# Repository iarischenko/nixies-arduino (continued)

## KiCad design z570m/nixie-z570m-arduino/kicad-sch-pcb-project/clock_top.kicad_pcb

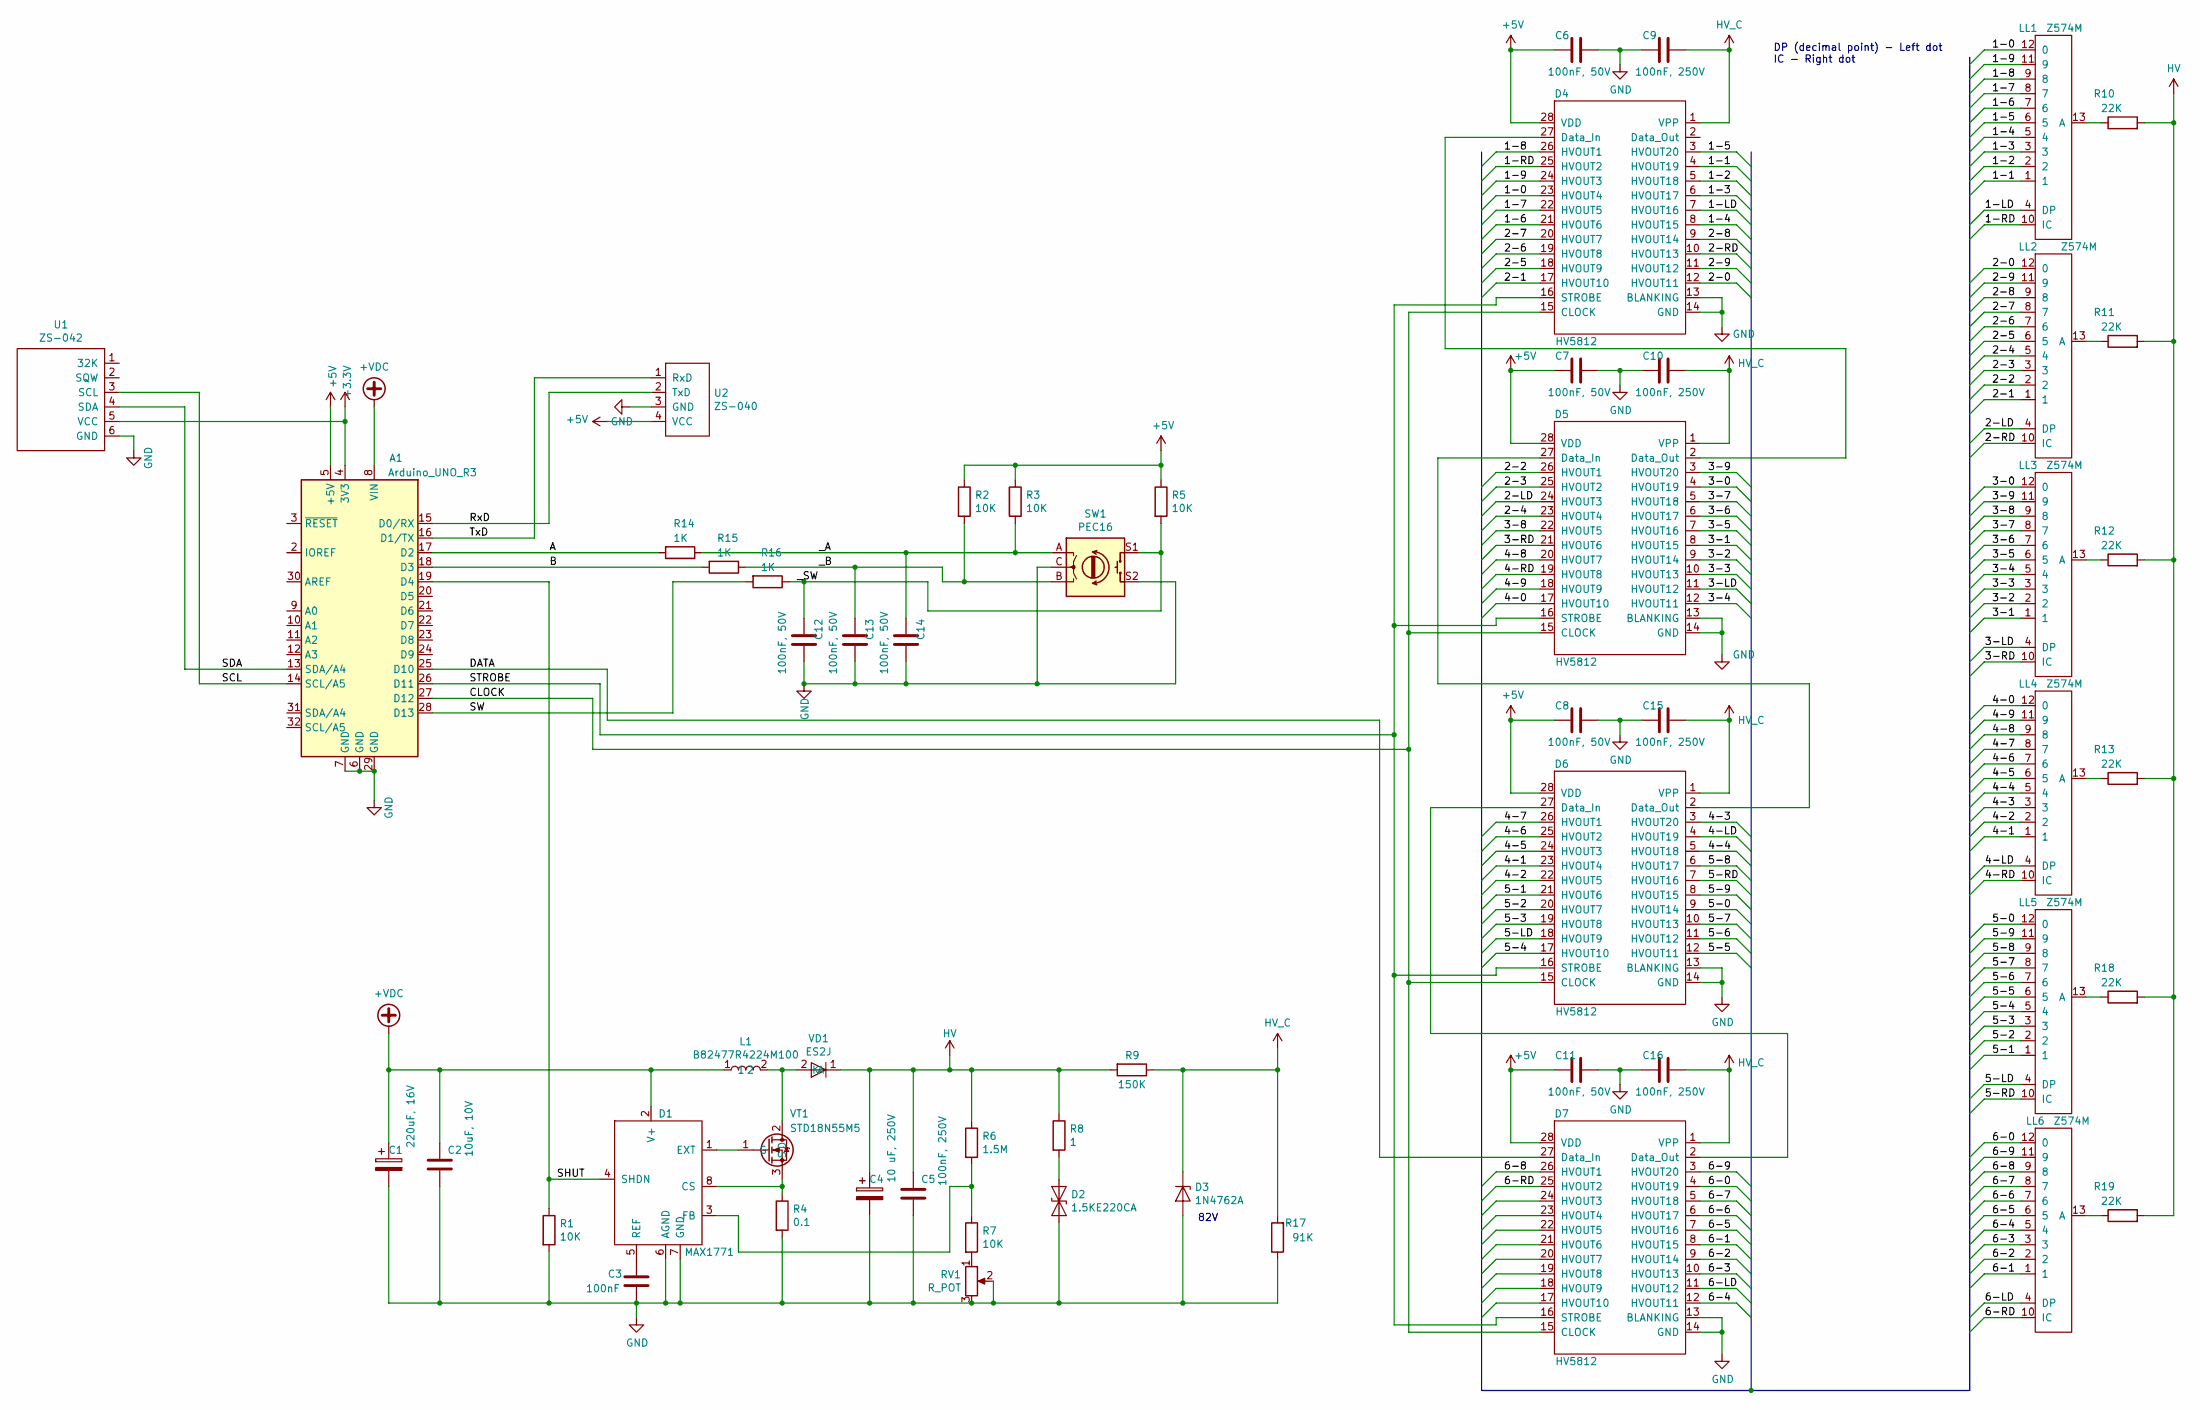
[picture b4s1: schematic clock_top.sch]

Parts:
A1: Arduino_UNO_R3
C1: 220uF, 16V; CP_Radial_D6.3mm_P2.50mm
C2: 10uF, 10V; C_1210_3225Metric_Pad1.42x2.65mm_HandSolder
C3: 100nF; C_0805_2012Metric_Pad1.15x1.40mm_HandSolder
C4: 10 uF, 250V; C_Axial_L22.0mm_D10.5mm_P27.50mm_Horizontal
C5, C9, C10, C15, C16: 100nF, 250V; C_1206_3216Metric_Pad1.42x1.75mm_HandSolder
C6, C7, C8, C11, C12, C13, C14: 100nF, 50V; C_0805_2012Metric_Pad1.15x1.40mm_HandSolder
D1: MAX1771; DIP-8_W7.62mm
D2: 1.5KE220CA; D_DO-201AE_P15.24mm_Horizontal
D3: 1N4762A; D_DO-41_SOD81_P10.16mm_Horizontal
D4, D5, D6, D7: HV5812; SOIC-28W_7.5x17.9mm_P1.27mm
L1: B82477R4224M100; L_12x12mm_H8mm
LL1, LL2, LL3, LL4, LL5, LL6: Z574M; Z570M
R1, R2, R3, R5, R7: 10K; R_0805_2012Metric_Pad1.15x1.40mm_HandSolder
R4: 0.1; R_2512_6332Metric_Pad1.52x3.35mm_HandSolder
R6: 1.5M; R_0805_2012Metric_Pad1.15x1.40mm_HandSolder
R8: 1; R_1206_3216Metric_Pad1.42x1.75mm_HandSolder
R9: 150K; R_0805_2012Metric_Pad1.15x1.40mm_HandSolder
R10, R11, R12, R13, R18, R19: 22K; R_0805_2012Metric_Pad1.15x1.40mm_HandSolder
R14, R15, R16: 1K; R_0805_2012Metric_Pad1.15x1.40mm_HandSolder
R17: 91K; R_0805_2012Metric_Pad1.15x1.40mm_HandSolder
RV1: R_POT; 3296W
SW1: PEC16; RotaryEncoder_Bouruns_PEC16
U1: ZS-042; zs-042
U2: ZS-040; zs-040
VD1: ES2J; D_SMB_Handsoldering
VT1: STD18N55M5; TO-252-2

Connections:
+3V3: A1.4 (3V3), U1.5 (VCC)
+5V: A1.5 (+5V), C6.2, C7.2, C8.2, C11.2, D4.28 (VDD), D5.28 (VDD), D6.28 (VDD), D7.28 (VDD), R2.1, R3.1, R5.1, U2.4 (VCC)
+VDC: A1.8 (VIN), C1.1, C2.1, D1.2 (V+), L1.1
/1-0: D4.23 (HVOUT4), LL1.12 (0)
/1-1: D4.4 (HVOUT19), LL1.1
/1-2: D4.5 (HVOUT18), LL1.2
/1-3: D4.6 (HVOUT17), LL1.3
/1-4: D4.8 (HVOUT15), LL1.5 (4)
/1-5: D4.3 (HVOUT20), LL1.6 (5)
/1-6: D4.21 (HVOUT6), LL1.7 (6)
/1-7: D4.22 (HVOUT5), LL1.8 (7)
/1-8: D4.26 (HVOUT1), LL1.9 (8)
/1-9: D4.24 (HVOUT3), LL1.11 (9)
/1-LD: D4.7 (HVOUT16), LL1.4 (DP)
/1-RD: D4.25 (HVOUT2), LL1.10 (IC)
/2-0: D4.12 (HVOUT11), LL2.12 (0)
/2-1: D4.17 (HVOUT10), LL2.1
/2-2: D5.26 (HVOUT1), LL2.2
/2-3: D5.25 (HVOUT2), LL2.3
/2-4: D5.23 (HVOUT4), LL2.5 (4)
/2-5: D4.18 (HVOUT9), LL2.6 (5)
/2-6: D4.19 (HVOUT8), LL2.7 (6)
/2-7: D4.20 (HVOUT7), LL2.8 (7)
/2-8: D4.9 (HVOUT14), LL2.9 (8)
/2-9: D4.11 (HVOUT12), LL2.11 (9)
/2-LD: D5.24 (HVOUT3), LL2.4 (DP)
/2-RD: D4.10 (HVOUT13), LL2.10 (IC)
/3-0: D5.4 (HVOUT19), LL3.12 (0)
/3-1: D5.8 (HVOUT15), LL3.1
/3-2: D5.9 (HVOUT14), LL3.2
/3-3: D5.10 (HVOUT13), LL3.3
/3-4: D5.12 (HVOUT11), LL3.5 (4)
/3-5: D5.7 (HVOUT16), LL3.6 (5)
/3-6: D5.6 (HVOUT17), LL3.7 (6)
/3-7: D5.5 (HVOUT18), LL3.8 (7)
/3-8: D5.22 (HVOUT5), LL3.9 (8)
/3-9: D5.3 (HVOUT20), LL3.11 (9)
/3-LD: D5.11 (HVOUT12), LL3.4 (DP)
/3-RD: D5.21 (HVOUT6), LL3.10 (IC)
/4-0: D5.17 (HVOUT10), LL4.12 (0)
/4-1: D6.23 (HVOUT4), LL4.1
/4-2: D6.22 (HVOUT5), LL4.2
/4-3: D6.3 (HVOUT20), LL4.3
/4-4: D6.5 (HVOUT18), LL4.5 (4)
/4-5: D6.24 (HVOUT3), LL4.6 (5)
/4-6: D6.25 (HVOUT2), LL4.7 (6)
/4-7: D6.26 (HVOUT1), LL4.8 (7)
/4-8: D5.20 (HVOUT7), LL4.9 (8)
/4-9: D5.18 (HVOUT9), LL4.11 (9)
/4-LD: D6.4 (HVOUT19), LL4.4 (DP)
/4-RD: D5.19 (HVOUT8), LL4.10 (IC)
/5-0: D6.9 (HVOUT14), LL5.12 (0)
/5-1: D6.21 (HVOUT6), LL5.1
/5-2: D6.20 (HVOUT7), LL5.2
/5-3: D6.19 (HVOUT8), LL5.3
/5-4: D6.17 (HVOUT10), LL5.5 (4)
/5-5: D6.12 (HVOUT11), LL5.6 (5)
/5-6: D6.11 (HVOUT12), LL5.7 (6)
/5-7: D6.10 (HVOUT13), LL5.8 (7)
/5-8: D6.6 (HVOUT17), LL5.9 (8)
/5-9: D6.8 (HVOUT15), LL5.11 (9)
/5-LD: D6.18 (HVOUT9), LL5.4 (DP)
/5-RD: D6.7 (HVOUT16), LL5.10 (IC)
/6-0: D7.4 (HVOUT19), LL6.12 (0)
/6-1: D7.8 (HVOUT15), LL6.1
/6-2: D7.9 (HVOUT14), LL6.2
/6-3: D7.10 (HVOUT13), LL6.3
/6-4: D7.12 (HVOUT11), LL6.5 (4)
/6-5: D7.7 (HVOUT16), LL6.6 (5)
/6-6: D7.6 (HVOUT17), LL6.7 (6)
/6-7: D7.5 (HVOUT18), LL6.8 (7)
/6-8: D7.26 (HVOUT1), LL6.9 (8)
/6-9: D7.3 (HVOUT20), LL6.11 (9)
/6-LD: D7.11 (HVOUT12), LL6.4 (DP)
/6-RD: D7.25 (HVOUT2), LL6.10 (IC)
/A: A1.17 (D2), R14.2
/B: A1.18 (D3), R15.2
/CLOCK: A1.27 (D12), D4.15 (CLOCK), D5.15 (CLOCK), D6.15 (CLOCK), D7.15 (CLOCK)
/DATA: A1.25 (D10), D7.27 (Data_In)
/RxD: A1.15 (D0/RX), U2.2 (TxD)
/SCL: A1.14 (SCL/A5), U1.3 (SCL)
/SDA: A1.13 (SDA/A4), U1.4 (SDA)
/SHUT: A1.19 (D4), D1.4 (SHDN), R1.1
/STROBE: A1.26 (D11), D4.16 (STROBE), D5.16 (STROBE), D6.16 (STROBE), D7.16 (STROBE)
/SW: A1.28 (D13), R16.2
/TxD: A1.16 (D1/TX), U2.1 (RxD)
/_A: C14.2, R3.2, R14.1, SW1.A
/_B: C13.2, R2.2, R15.1, SW1.B
/_SW: C12.2, R5.2, R16.1, SW1.S1
GND: A1.6 (GND), A1.7 (GND), A1.29 (GND), C1.2, C2.2, C3.2, C4.2, C5.2, C6.1, C7.1, C8.1, C9.2, C10.2, C11.1, C12.1, C13.1, C14.1, C15.2, C16.2, D1.6 (AGND), D1.7 (GND), D2.2 (A2), D3.2 (A), D4.13 (BLANKING), D4.14 (GND), D5.13 (BLANKING), D5.14 (GND), D6.13 (BLANKING), D6.14 (GND), D7.13 (BLANKING), D7.14 (GND), R1.2, R4.2, R17.1, RV1.2, RV1.3, SW1.C, SW1.S2, U1.6 (GND), U2.3 (GND)
HV: C4.1, C5.1, R6.1, R8.1, R9.2, R10.2, R11.2, R12.2, R13.2, R18.2, R19.2, VD1.1 (K)
HV_C: C9.1, C10.1, C15.1, C16.1, D3.1 (K), D4.1 (VPP), D5.1 (VPP), D6.1 (VPP), D7.1 (VPP), R9.1, R17.2
unnamed: C3.1, D1.5 (REF)
unnamed: D1.1 (EXT), VT1.1 (G)
unnamed: D1.3 (FB), R6.2, R7.1
unnamed: D1.8 (CS), R4.1, VT1.3 (S)
unnamed: D2.1 (A1), R8.2
unnamed: D4.27 (Data_In), D5.2 (Data_Out)
unnamed: D5.27 (Data_In), D6.2 (Data_Out)
unnamed: D6.27 (Data_In), D7.2 (Data_Out)
unnamed: L1.2, VD1.2 (A), VT1.2 (D)
unnamed: LL1.13 (A), R10.1
unnamed: LL2.13 (A), R11.1
unnamed: LL3.13 (A), R12.1
unnamed: LL4.13 (A), R13.1
unnamed: LL5.13 (A), R18.1
unnamed: LL6.13 (A), R19.1
unnamed: R7.2, RV1.1

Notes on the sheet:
DP (decimal point) - Left dot IC - Right dot
82V

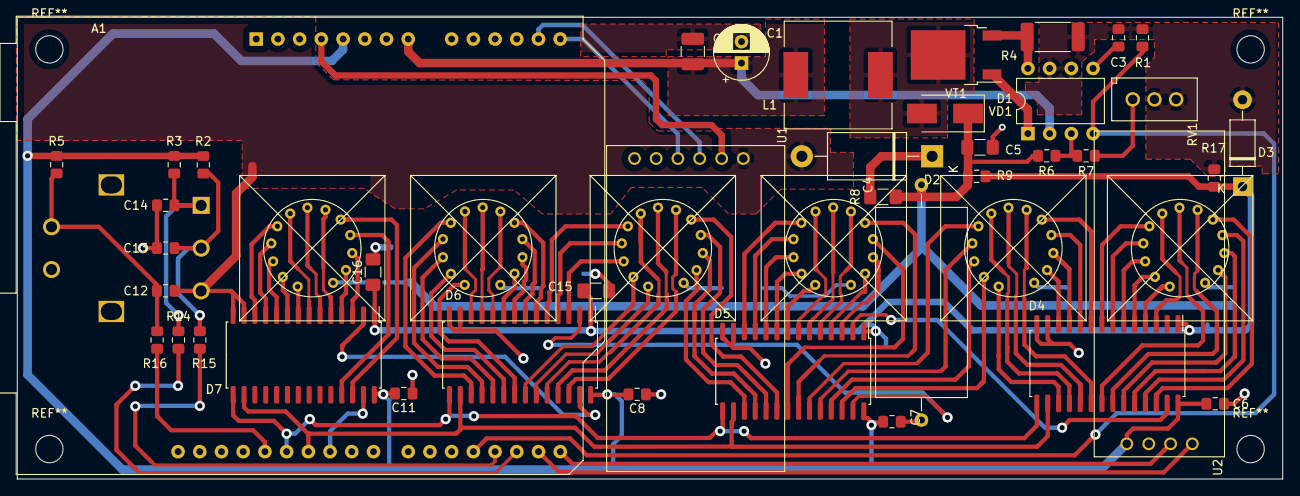
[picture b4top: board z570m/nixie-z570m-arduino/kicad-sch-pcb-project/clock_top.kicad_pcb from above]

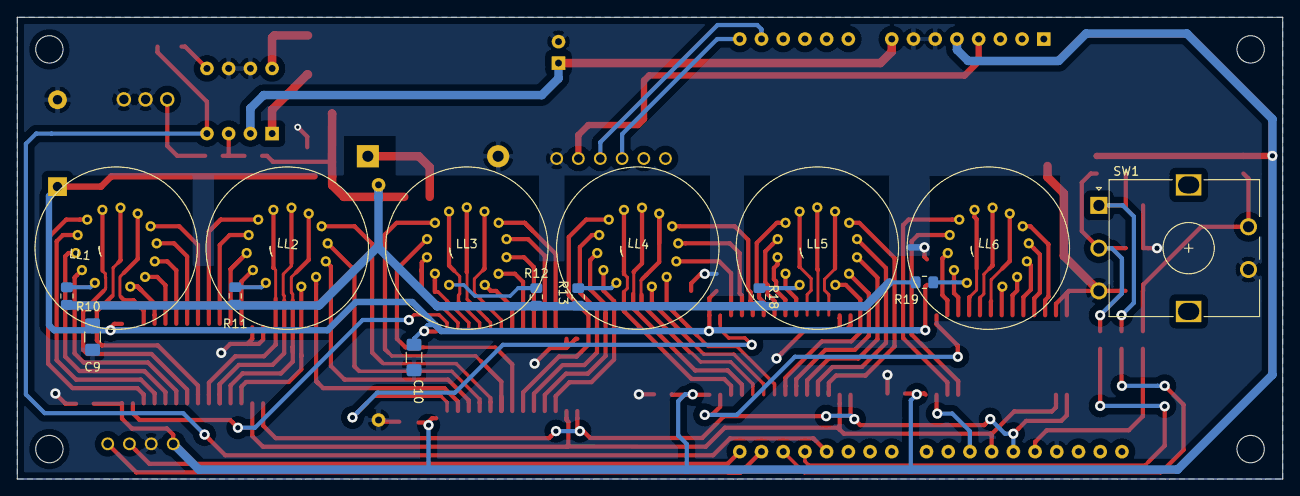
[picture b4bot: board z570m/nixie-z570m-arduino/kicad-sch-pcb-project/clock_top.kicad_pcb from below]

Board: 2 copper layers, 148.0 x 54.0 mm, 56 parts (15 on the bottom side), 108 nets.

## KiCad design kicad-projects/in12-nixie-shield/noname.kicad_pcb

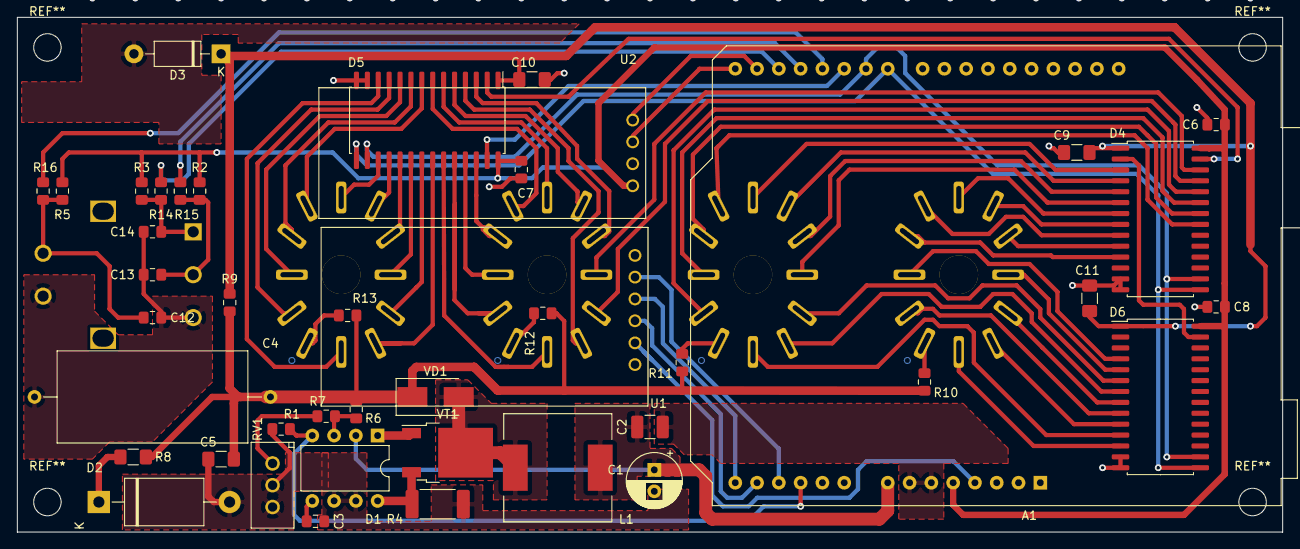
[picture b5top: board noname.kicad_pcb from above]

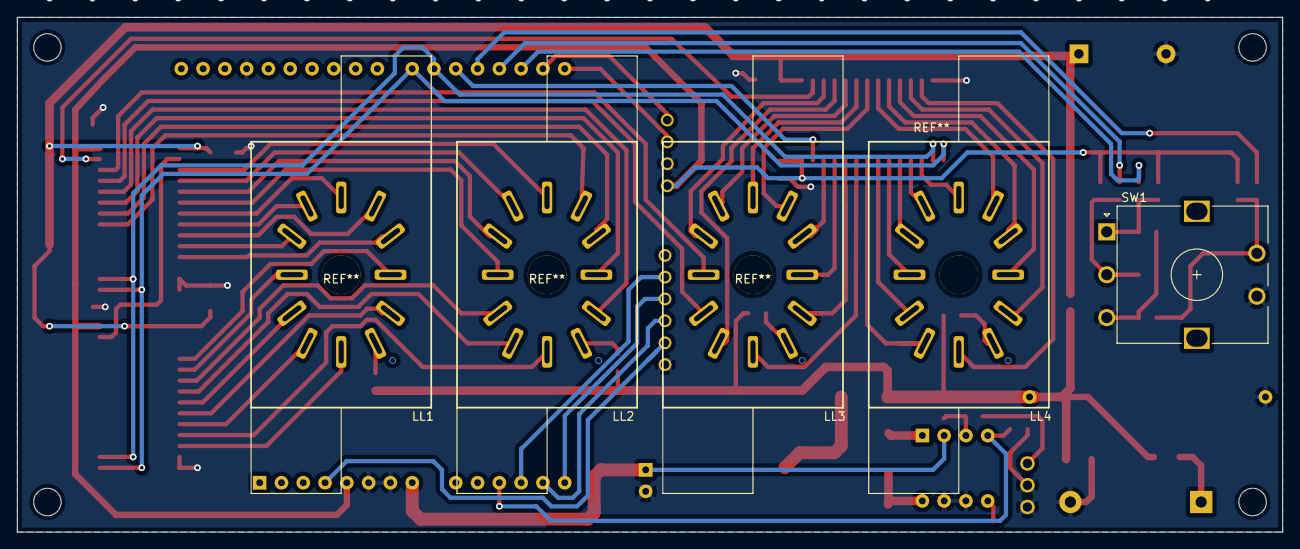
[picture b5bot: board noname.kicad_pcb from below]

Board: 2 copper layers, 147.5 x 60.0 mm, 48 parts (5 on the bottom side), 78 nets.

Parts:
A1: Arduino_UNO_R3
C1: 220uF, 16V; CP_Radial_D6.3mm_P2.50mm
C2: 10uF, 10V; C_1210_3225Metric_Pad1.42x2.65mm_HandSolder
C3: 100nF; C_0805_2012Metric_Pad1.15x1.40mm_HandSolder
C4: 10 uF, 250V; C_Axial_L22.0mm_D10.5mm_P27.50mm_Horizontal
C5, C9, C10, C11: 100nF, 250V; C_1206_3216Metric_Pad1.42x1.75mm_HandSolder
C6, C7, C8, C12, C13, C14: 100nF, 50V; C_0805_2012Metric_Pad1.15x1.40mm_HandSolder
D1: MAX1771; DIP-8_W7.62mm
D2: 1.5KE220CA; D_DO-201AE_P15.24mm_Horizontal
D3: 1N4764A; D_DO-41_SOD81_P10.16mm_Horizontal
D4, D5, D6: HV5812; SOIC-28W_7.5x17.9mm_P1.27mm
L1: B82477R4224M100; L_12x12mm_H8mm
LL1, LL2, LL3, LL4: IN-12B; PL31
R1, R2, R3, R5, R7: 10K; R_0805_2012Metric_Pad1.15x1.40mm_HandSolder
R4: 0.1; R_2512_6332Metric_Pad1.52x3.35mm_HandSolder
R6: 1.5M; R_0805_2012Metric_Pad1.15x1.40mm_HandSolder
R8: 1; R_1206_3216Metric_Pad1.42x1.75mm_HandSolder
R9: 150K; R_0805_2012Metric_Pad1.15x1.40mm_HandSolder
R10, R11, R12, R13: 22K; R_0805_2012Metric_Pad1.15x1.40mm_HandSolder
R14, R15, R16: 1K; R_0805_2012Metric_Pad1.15x1.40mm_HandSolder
RV1: R_POT; 3296W
SW1: PEC16; RotaryEncoder_Bouruns_PEC16
U1: ZS-042; zs-042
U2: ZS-040; zs-040
VD1: ES2J; D_SMB_Handsoldering
VT1: STD18N55M5; TO-252-2

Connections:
+3V3: A1.4, U1.5
+5V: A1.5, C6.2, C7.2, C8.2, D4.28, D5.28, D6.28, R2.1, R3.1, R5.1, U2.4
+VDC: A1.8, C1.1, C2.1, D1.2, L1.1
/1-0: D6.9, LL1.2
/1-1: D6.10, LL1.11
/1-2: D6.8, LL1.10
/1-3: D6.5, LL1.9
/1-4: D4.10, LL1.8
/1-5: D4.8, LL1.7
/1-6: D4.7, LL1.6
/1-7: D4.9, LL1.5
/1-8: D4.11, LL1.4
/1-9: D6.4, LL1.3
/1-.: D6.12, LL1.12
/2-0: D4.24, LL2.2
/2-1: D6.7, LL2.11
/2-2: D6.6, LL2.10
/2-3: D4.6, LL2.9
/2-4: D4.5, LL2.8
/2-5: D4.4, LL2.7
/2-6: D4.3, LL2.6
/2-7: D4.21, LL2.5
/2-8: D4.22, LL2.4
/2-9: D4.23, LL2.3
/2-.: D6.11, LL2.12
/3-0: D5.24, LL3.2
/3-1: D5.4, LL3.11
/3-2: D4.25, LL3.10
/3-3: D4.26, LL3.9
/3-4: D5.3, LL3.8
/3-5: D5.5, LL3.7
/3-6: D5.6, LL3.6
/3-7: D5.7, LL3.5
/3-8: D5.26, LL3.4
/3-9: D5.25, LL3.3
/3-.: D5.23, LL3.12
/4-0: D5.11, LL4.2
/4-1: D5.22, LL4.11
/4-2: D5.21, LL4.10
/4-3: D5.20, LL4.9
/4-4: D5.19, LL4.8
/4-5: D5.18, LL4.7
/4-6: D5.17, LL4.6
/4-7: D5.8, LL4.5
/4-8: D5.9, LL4.4
/4-9: D5.10, LL4.3
/4-.: D5.12, LL4.12
/A: A1.17, R14.2
/B: A1.18, R15.2
/CLOCK: A1.22, D4.15, D5.15, D6.15
/D-IN-OUT-1-2: D4.2, D6.27
/DATA: A1.20, D5.27
/RT_INT: A1.12, U1.2
/RxD: A1.15, U2.2
/SCL: A1.14, U1.3
/SDA: A1.13, U1.4
/SHUT: A1.11, D1.4, R1.1
/STROBE: A1.21, D4.16, D5.16, D6.16
/SW: A1.19, R16.2
/TxD: A1.16, U2.1
/_A: C14.2, R3.2, R14.1, SW1.A
/_B: C13.2, R2.2, R15.1, SW1.B
/_SW: C12.2, R5.2, R16.1, SW1.S1
GND: A1.6, A1.7, A1.29, C1.2, C2.2, C3.2, C4.2, C5.2, C6.1, C7.1, C8.1, C9.2, C10.2, C11.2, C12.1, C13.1, C14.1, D1.6, D1.7, D2.2, D3.2, D4.13, D4.14, D5.13, D5.14, D6.13, D6.14, R1.2, R4.2, RV1.2, RV1.3, SW1.C, SW1.S2, U1.6, U2.3
HV: C4.1, C5.1, R6.1, R8.1, R9.2, R10.2, R11.2, R12.2, R13.2, VD1.1
HV_C: C9.1, C10.1, C11.1, D3.1, D4.1, D5.1, D6.1, R9.1
unnamed: C3.1, D1.5
unnamed: D1.1, VT1.1
unnamed: D1.3, R6.2, R7.1
unnamed: D1.8, R4.1, VT1.3
unnamed: D2.1, R8.2
unnamed: D4.27, D5.2
unnamed: L1.2, VD1.2, VT1.2
unnamed: LL1.1, R10.1
unnamed: LL2.1, R11.1
unnamed: LL3.1, R12.1
unnamed: LL4.1, R13.1
unnamed: R7.2, RV1.1

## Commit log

2020-03-16 Arduino sketch: initial version
    The sketch does the following:
    - shows current time and date over nixies tubes: 4 digits and
    4 dots
    - allows to change mode by encoder: show year, day-month,
    hours-minuties, minuties-seconds
    - allows to setup time with encoder for selected mode
2020-03-16 shematic: nixies board
    The board consists of:
    - 4 IN12B nixies tubes
    - PEC16 encoder
    - MAX1771 boots converter
    - connection for Arduino UNO R3 board
    - connection for ZS-042 RTC board
2020-03-16 Panelized nixies PCB
    Top and bottom CU layers.
2020-03-16 README.md is created
    known issues with pcb board are noted
2020-03-16 Update README.md
    Added clock photo
2020-06-07 nixie-in12-arduino.ino is moved to nixie-in12-arduino folder
2020-06-07 z570m arduino shield sch
2020-06-07 sketch for z570m sheild
    Is is a copy of sketch for IN12 tubes.
2020-06-07 accidentally removed ; : fixed
2020-06-08 updated configuration for digits 5 and 6
2020-06-08 fixed configuration for tubes 1,2,3 and 4
2020-06-09 arduino - z570m nixies tubes
    The shield has 6 nixies tubes. The tubes are used to
    show calenar in format year-moth-day or date in format
    hours-minities-seconds. On board PEC16 encoder is used
    to switch from calendar to date and back. The PEC16 button
    is used to setup calendar or adjust date.
2020-07-09 arduino - IN12 nixies tubes
    The shield has 6 nixies tubes. The tubes are used to
    show calenar in format year-moth-day or date in format
    hours-minities-seconds. On board PEC16 encoder is used
    to switch from calendar to date and back. The PEC16 button
    is used to setup calendar or adjust date.
2020-07-19 digits shift
    In order to prevent tubes catones poisoning need to time to time light up
    all digits. Show digits from 0 till 9 looks ugly, digits show order is
    changed from fixed to random.
    Before commit:
    .....
    111111
2020-10-03 Kicad sch and pcb files
    for IN12v1, IN12v and z570m nixie tubes
2020-10-04 Readme.md is updated
2020-10-04 Readmi.md is update
2020-10-04 README.md is updated: added second video
2023-06-16 Added: in12 v3 version
    - arduino boards is replaced with stm32 based board
    - shield is updated: more space beetween tubes, unused parts
    are removed (in progress)
    - created case 3d model (in progress)
2023-06-21 stm32: initial code
    - fusb302: sanity check: read DEVICE_ID reg
    - stm32 cdc: sanity check: usb-cdc echo example
2023-06-27 FUSB302: import PD_Micro code
    https://github.com/ryan-ma/PD_Micro
    The code will be ported for stm32 target.
2023-06-30 usart: libopencm3-examples
    usart_irq_printf.c is taken from the libopencm3-examples.
2023-06-30 usart1: adopted for my project
2023-07-03 poring: PD_micro & usart example
    ported, not tested
2023-07-07 Removed cache file
2023-07-07 FUSB302: communication with PS works
    log example:
    6:FUSB302 ver ID:B_revB
    9:USB attached CC2 vRd-3.0
    104:RX Src_Cap id=0 raw=0x41A1
    105:obj0=0x0a11912c
    105:obj1=0x0012d12c
2023-07-08 FUSB302: logs fixed
    PS power options log is fixed:
    6:FUSB302 ver ID:B_revB
    9:USB attached CC1 vRd-3.0
    158:RX Src_Cap id=0 raw=0x71A1
    158:obj0=0x0801912c
    158:obj1=0x0002d12c
2023-07-08 git repo: refactor
    z570m is moved to z570m branch.
    in12 will be in master.
2023-07-08 z570 is moved to z570 branch
2023-07-08 git repo refactor: rm all
2023-07-08 git repo refactor: v1 (in12, arduino 4 tubes)
2023-07-08 git repo refactor: v2 in12, 6 tubes, arduino
2023-07-08 git repo refactor: v3 6 tubes, stm32
2023-07-11 stm32: rtc sanity check
    print to uart current date with ctime() function.
2023-08-31 pcb: revision bump
    stm32f103: revison 2
    - added: D+ to +5V (fixed error: unable to enumerate device)
    - added: usb phy int pin pull up to +3.3v (fixed no irq from phy)
    - moved: JTAG connector is moved to bottom layer
    clock-top (nixie shild): revision 1, initial version
    removed pf-info-cache (temp kicad file)
2023-10-18 stm32: nixie tubes & pec16
    Initial implementation for nixie tubes (hv5812) and pec16 encoder.
2023-11-05 nixie case: free cad project
    1 - main case
    2 - back cover
    It tooks around 100ml of photopolymer resin to print out the case.
    You will need 4 3x40 screw to assemble pcb with main case.
    Main case and back cover are connected with a latch.
2023-11-10 stm32 nixie clock
    - press pec16 button to setup clock
    - rtc calibration value is set in the Makefile
    - stop condition hack: recover i2c module after reset
    - operation votage 9~12 volts
    - nixie tubes: show digits, refresh
2024-01-21 README.md updated: added v3 video
